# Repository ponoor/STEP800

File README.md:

# STEP800
8-axis stepper motor driver for Open Sound Control

STEP800 is a 8-axis stepper motor driver designed for art or design projects. STEP800 combines the following elements into one single board:

- [Arduino Zero](https://www.arduino.cc/en/Guide/ArduinoZero)
- Ethernet shield
- 8 stepper motor drivers
- Sensor inputs for homing

The current firmware is focused on working with [Open Sound Control](http://opensoundcontrol.org/) (OSC) via Ethernet, which is a common protocol for creative coding environments, like openFrameworks, Processing, Max, Unity, or Touch Designer.

Stepper driver chips are STMicroelectronics's [L6470](https://www.st.com/en/motor-drivers/l6470.html) which provide most of functionalities as a stepper driver.

Friend of STEP800 : [STEP400](https://github.com/ponoor/STEP400)

## Store
https://ponoor.com/en/shop/

## Documentation
https://ponoor.com/en/docs/step-series/

Forum: https://github.com/ponoor/step-series-support/discussions

## Repository Contents
### Firmware

**Important Note:**
The latest firmware is available at [STEP-series Universal Firmware](https://github.com/ponoor/step-series-universal-firmware) repository. Following directories and Releases are not maintained anymore. 

These 2 folders contain same codes.
- [/STEP800_firmware](https://github.com/ponoor/STEP800/tree/main/STEP800_firmware) : Arduino Sketch folder
- [/firmware-platformIO/STEP800_firmware](https://github.com/ponoor/STEP800/tree/main/firmware-platformIO/STEP800_firmware) : PlatformIO folder

### Hardware
[/hardware](https://github.com/ponoor/STEP800/tree/main/hardware) : Eagle design files, BOM lists, and a schematics PDF

### Others
[/configTool](https://github.com/ponoor/STEP800/tree/main/configTool) : The configuration tool consists of a html and JavaScritpts.

## Firmware dependency
- **[OSC Library](https://github.com/CNMAT/OSC)** from CNMAT
- **[Ponoor L6470 Library](https://github.com/ponoor/Ponoor_L6470_Library)**
- **[ArduinoJSON Library](https://arduinojson.org/)**
- **[Adafruit SleepyDog Arduino Library](https://github.com/adafruit/Adafruit_SleepyDog)**

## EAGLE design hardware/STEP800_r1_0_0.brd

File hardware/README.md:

# Diagram
```mermaid
flowchart LR
	MCU ---|SPI/SERCOM4| W5500 --- Ethernet
	MCU --- |SPI/SERCOM3|L6470 --> Motor
  MCU --> |SPI/SERCOM2|74HC165 --> 74HC595 --> MCU
	HomeSw -->|SW| L6470
	DIPSW --> 74HC165
	74HC595 --> Brake
  ```
  
  Check the [document](https://ponoor.com/en/docs/step-series/technical-information/hardware-step800/) for details.

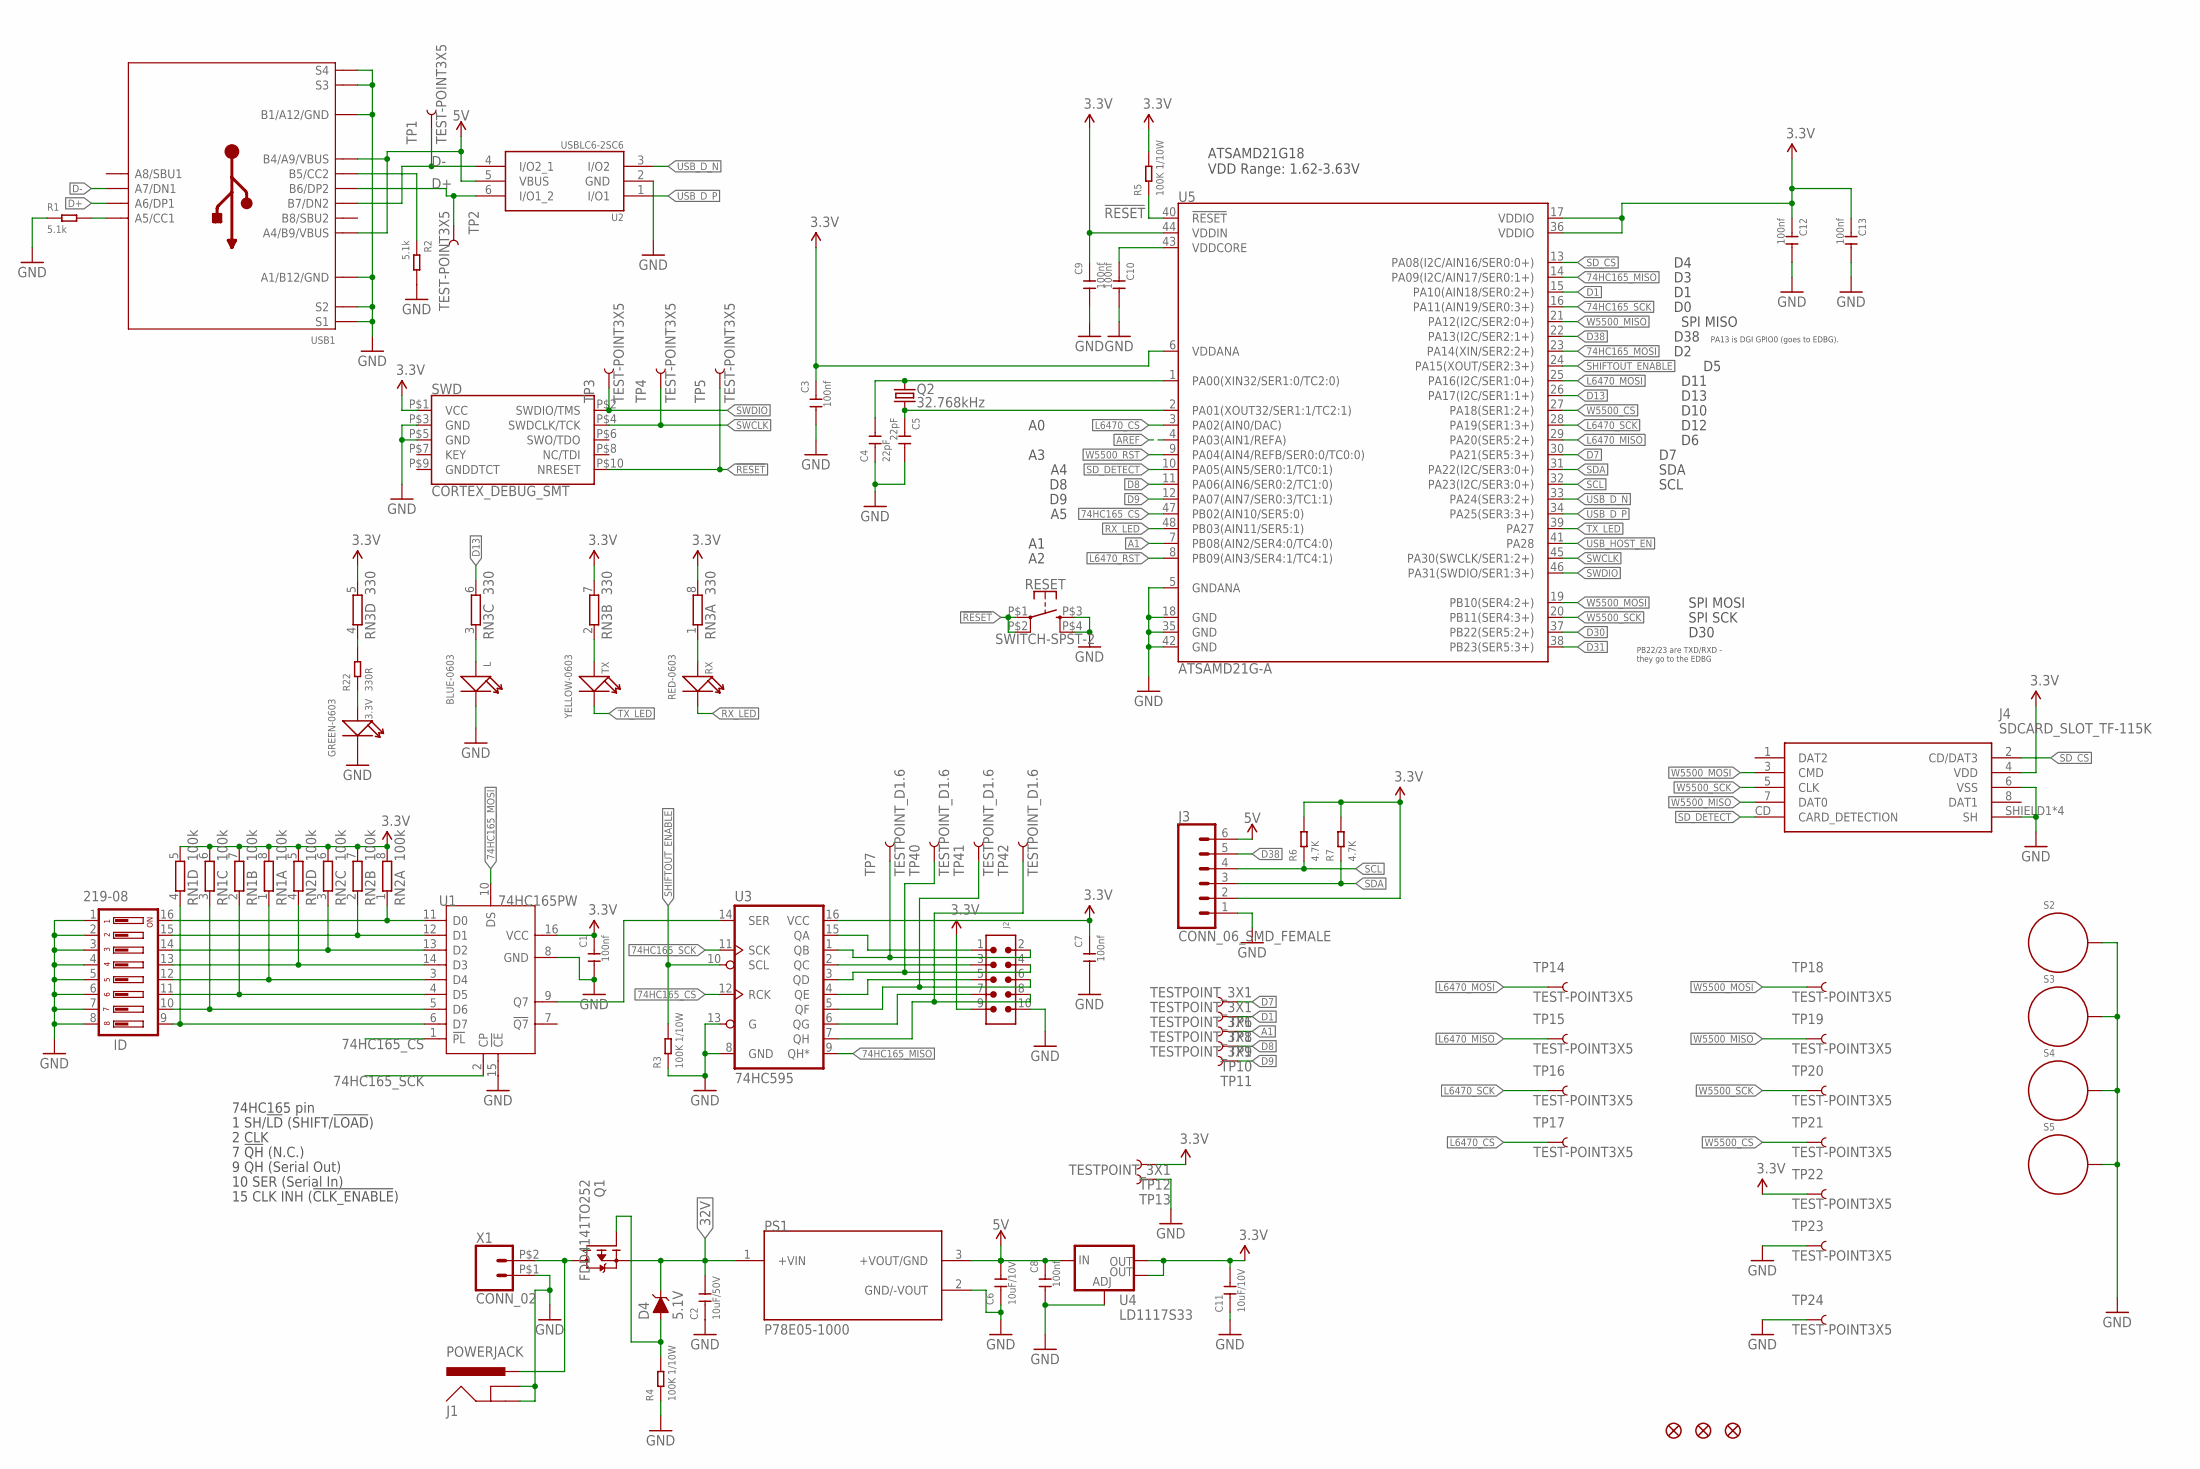
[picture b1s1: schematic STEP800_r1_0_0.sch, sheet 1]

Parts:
3.3V: GREEN-0603; LED-0603
C1, C3, C7, C8, C9, C10, C12, C13: 100nf; C0402
C2: 10uF/50V; C1206
C4, C5: 22pF; C0402
C6: 10uF/10V; C1206
C11: 10uF/10V; C0805
D4: 5.1V; SOD-323
FD1, FD2, FD3: FIDUCIAL1X2; FIDUCIAL-1X2
ID: 219-08; CTS-219-08
J1: POWERJACK; POWERJACK_SLOT
J2: 6120XX21621_61201021621; 61201021621
J3: CONN_06_SMD_FEMALE; 1X06-SMD-FEMALE
J4: SDCARD_SLOT_TF-115K; TF-115K
L: BLUE-0603; LED-0603
PS1: P78E05-1000; CONV_P78E05-1000
Q1: FDD4141TO252; TO252
Q2: 32.768kHz; FC-135
R1, R2: 5.1k; R0603
R3, R4, R5: 100K 1/10W; R0603
R6, R7: 4.7K; R0603
R22: 330R; R0603
RESET: SWITCH-SPST-2; SKRP
RN1, RN2: 100k; CAY16_LONG_W
RN3: 330; CAY16_LONG_W
RX: RED-0603; LED-0603
S2, S3, S4, S5: STANDOFF_ELECTRICAL; STANDOFF-ELECTRICAL
SWD: CORTEX_DEBUG_SMT; 20021121-00010C4LF
TP1, TP2, TP3, TP4, TP5, TP14, TP15, TP16, TP17, TP18, TP19, TP20, TP21, TP22, TP23, TP24: TEST-POINT3X5; PAD.03X.05
TP6, TP8, TP9, TP10, TP11, TP12, TP13: TESTPOINT_3X1
TP7, TP40, TP41, TP42: TESTPOINT_D1.6
TX: YELLOW-0603; LED-0603
U1: 74HC165PW; TSSOP16
U2: USBLC6-2SC6; SOT23-6L
U3: 74HC595; TSSOP16
U4: LD1117S33; SOT223
U5: ATSAMD21G-A; TQFP-48
USB1: USB-C_USB2.0-TYPE-C
X1: CONN_02; WJ25C-B-7.62-2P

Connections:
3.3V: C1.1, C3.1, C7.1, C9.1, C11.2, C12.1, C13.1, J2.9, J3.2, J4.4 (VDD), R5.2, R6.2, R7.2, RN1.5 (2), RN1.6 (2), RN1.7 (2), RN1.8 (2), RN2.5 (2), RN2.6 (2), RN2.7 (2), RN2.8 (2), RN3.5 (2), RN3.7 (2), RN3.8 (2), SWD.P$1 (VCC), TP12.P$1, TP22.P$1, U1.16 (VCC), U3.16 (VCC), U4.2 (OUT), U4.4 (OUT), U5.6 (VDDANA), U5.17 (VDDIO), U5.36 (VDDIO), U5.44 (VDDIN); also elsewhere on the board
5V: C6.2, C8.1, J3.6, PS1.3 (+VOUT/GND), U2.5 (VBUS), U4.3 (IN), USB1.A4_B9 (A4/B9/VBUS), USB1.B4_A9 (B4/A9/VBUS); also elsewhere on the board
32V: C2.2, D4.C, PS1.1 (+VIN), Q1.2 (S); also elsewhere on the board
74HC165_CS: U1.1 (!PL), U3.12 (RCK), U5.47 (PB02(AIN10/SER5:0))
74HC165_MISO: U3.9 (QH*), U5.14 (PA09(I2C/AIN17/SER0:1+))
74HC165_MOSI: U1.10 (DS), U5.23 (PA14(XIN/SER2:2+))
74HC165_SCK: U1.2 (CP), U3.11 (SCK), U5.16 (PA11(AIN19/SER0:3+))
!RESET: R5.1, RESET.P$1 (1), RESET.P$2 (2), SWD.P$10 (NRESET), TP5.P$1, U5.40 (!RESET!)
A1: TP9.P$1, U5.7 (PB08(AIN2/SER4:0/TC4:0))
AREF: U5.4 (PA03(AIN1/REFA))
D1: TP8.P$1, U5.15 (PA10(AIN18/SER0:2+))
D7: TP6.P$1, U5.30 (PA21(SER5:3+))
D8: TP10.P$1, U5.11 (PA06(AIN6/SER0:2/TC1:0))
D9: TP11.P$1, U5.12 (PA07(AIN7/SER0:3/TC1:1))
D13: RN3.6 (2), U5.26 (PA17(I2C/SER1:1+))
D30: U5.37 (PB22(SER5:2+))
D31: U5.38 (PB23(SER5:3+))
D38: J3.5, U5.22 (PA13(I2C/SER2:1+))
D+: TP2.P$1, U2.6 (I/O1_2), USB1.A6 (A6/DP1), USB1.B6 (B6/DP2)
D-: TP1.P$1, U2.4 (I/O2_1), USB1.A7 (A7/DN1), USB1.B7 (B7/DN2)
GND: 3.3V.-, C1.2, C2.1, C3.2, C4.1, C5.2, C6.1, C7.2, C8.2, C9.2, C10.2, C11.1, C12.2, C13.2, ID.1, ID.2, ID.3, ID.4, ID.5, ID.6, ID.7, ID.8, J1.P$33 (GNDBREAK), J1.P$34 (GNDBREAK), J1.P$35 (GNDBREAK), J1.P$36 (GNDBREAK), J1.P$37 (GNDBREAK), J1.P$38 (GNDBREAK), J1.P$39 (GNDBREAK), J1.P$40 (GNDBREAK), J1.P$41 (GNDBREAK), J1.P$42 (GNDBREAK), J1.P$43 (GNDBREAK), J1.P$44 (GNDBREAK), J1.P$45 (GNDBREAK), J1.P$46 (GNDBREAK), J1.P$47 (GNDBREAK), J1.P$48 (GNDBREAK), J1.P$49 (GNDBREAK), J1.P$50 (GNDBREAK), J1.P$51 (GNDBREAK), J1.P$52 (GNDBREAK), J1.P$53 (GNDBREAK), J1.P$54 (GNDBREAK), J1.P$55 (GNDBREAK), J1.P$56 (GNDBREAK), J1.P$63 (GND), J1.P$64 (GND), J1.P$65 (GND), J1.P$66 (GND), J1.P$67 (GND), J1.P$68 (GND), J1.P$69 (GND), J1.P$70 (GND), J1.P$71 (GND), J1.P$72 (GND), J1.P$73 (GND), J1.P$74 (GND), J1.P$75 (GND), J1.P$76 (GND), J1.P$77 (GND), J1.P$78 (GND), J1.P$79 (GND), J1.P$80 (GND), J1.P$81 (GND), J1.P$82 (GND), J1.P$83 (GND), J1.P$84 (GND), J1.P$85 (GND), J2.10, J3.1, J4.6 (VSS), J4.SHIELD1 (SH), J4.SHIELD2 (SH), J4.SHIELD3 (SH), J4.SHIELD4 (SH), L.-, PS1.2 (GND/-VOUT), R1.1, R2.2, R3.1, R4.1, RESET.P$3 (3), RESET.P$4 (4), S2.P1, S3.P1, S4.P1, S5.P1, SWD.P$3 (GND), SWD.P$5 (GND), TP13.P$1, TP23.P$1, TP24.P$1, U1.8 (GND), U1.15 (!CE), U2.2 (GND), U3.8 (GND), U3.13 (G), U4.1 (ADJ), U5.5 (GNDANA), U5.18 (GND), U5.35 (GND), U5.42 (GND), USB1.A1_B12 (A1/B12/GND), USB1.B1_A12 (B1/A12/GND), USB1.S7 (S1), USB1.S8 (S1), USB1.S9 (S1), USB1.S10 (S1), USB1.S11 (S1), USB1.S12 (S1), USB1.S13 (S1), USB1.S14 (S1), USB1.S15 (S1), USB1.S16 (S3), USB1.S17 (S3), USB1.S18 (S3), USB1.S19 (S3), USB1.S20 (S3), USB1.S21 (S3), USB1.S22 (S3), USB1.S23 (S3), USB1.S24 (S3), USB1.S25 (S3), USB1.S26 (S3), USB1.S27 (S3), USB1.S29 (S2), USB1.S30 (S2), USB1.S31 (S2), USB1.S32 (S2), USB1.S33 (S2), USB1.S34 (S2), USB1.S35 (S2), USB1.S36 (S2), USB1.S37 (S4), USB1.S38 (S4), USB1.S39 (S4), USB1.S40 (S4), USB1.S41 (S4), USB1.S42 (S4), USB1.S43 (S4), USB1.S44 (S4), USB1.S45 (S4), USB1.S46 (S4), USB1.S47 (S4), USB1.S48 (S4), X1.P$1 (1); also elsewhere on the board
L6470_CS: TP17.P$1, U5.3 (PA02(AIN0/DAC)); also elsewhere on the board
L6470_MISO: TP15.P$1, U5.29 (PA20(SER5:2+)); also elsewhere on the board
L6470_MOSI: TP14.P$1, U5.25 (PA16(I2C/SER1:0+)); also elsewhere on the board
L6470_RST: U5.8 (PB09(AIN3/SER4:1/TC4:1)); also elsewhere on the board
L6470_SCK: TP16.P$1, U5.28 (PA19(SER1:3+)); also elsewhere on the board
unnamed: C4.2, Q2.P$2 (2), U5.1 (PA00(XIN32/SER1:0/TC2:0))
unnamed: ID.16, RN2.1, U1.11 (D0)
unnamed: D4.A, Q1.1 (G), R4.2
unnamed: ID.15, RN2.2 (1), U1.12 (D1)
unnamed: ID.14, RN2.3 (1), U1.13 (D2)
unnamed: C5.1, Q2.P$1 (1), U5.2 (PA01(XOUT32/SER1:1/TC2:1))
unnamed: U1.9 (Q7), U3.14 (SER)
unnamed: RN3.1, RX.+
unnamed: ID.13, RN2.4 (1), U1.14 (D3)
unnamed: ID.12, RN1.1, U1.3 (D4)
unnamed: ID.11, RN1.2 (1), U1.4 (D5)
unnamed: RN3.2 (1), TX.+
unnamed: L.+, RN3.3 (1)
unnamed: R22.2, RN3.4 (1)
unnamed: J2.3, U3.2 (QC)
unnamed: ID.10, RN1.3 (1), U1.5 (D6)
unnamed: J2.2, TP7.1, U3.1 (QB)
unnamed: J2.1, U3.15 (QA)
unnamed: ID.9, RN1.4 (1), U1.6 (D7)
unnamed: J2.4, TP40.1, U3.3 (QD)
unnamed: J2.5, U3.4 (QE)
unnamed: J2.6, TP41.1, U3.5 (QF)
unnamed: J2.7, U3.6 (QG)
unnamed: J2.8, TP42.1, U3.7 (QH)
unnamed: R2.1, USB1.B5 (B5/CC2)
unnamed: 3.3V.+, R22.1
unnamed: R1.2, USB1.A5 (A5/CC1)
RX_LED: RX.-, U5.48 (PB03(AIN11/SER5:1))
SCL: J3.4, R6.1, U5.32 (PA23(I2C/SER3:0+))
SDA: J3.3, R7.1, U5.31 (PA22(I2C/SER3:0+))
SD_CS: J4.2 (CD/DAT3), U5.13 (PA08(I2C/AIN16/SER0:0+))
SD_DETECT: J4.CD (CARD_DETECTION), U5.10 (PA05(AIN5/SER0:1/TC0:1))
SHIFTOUT_ENABLE: R3.2, U3.10 (SCL), U5.24 (PA15(XOUT/SER2:3+))
SWCLK: SWD.P$4 (SWDCLK/TCK), TP4.P$1, U5.45 (PA30(SWCLK/SER1:2+))
SWDIO: SWD.P$2 (SWDIO/TMS), TP3.P$1, U5.46 (PA31(SWDIO/SER1:3+))
TX_LED: TX.-, U5.39 (PA27)
USB_D_N: U2.3 (I/O2), U5.33 (PA24(SER3:2+))
USB_D_P: U2.1 (I/O1), U5.34 (PA25(SER3:3+))
USB_HOST_EN: U5.41 (PA28)
VDDCORE1: C10.1, U5.43 (VDDCORE)
VRAW: J1.P$2 (PWR), J1.P$3 (PWR), J1.P$4 (PWR), J1.P$5 (PWR), J1.P$6 (PWR), J1.P$7 (PWR), J1.P$8 (PWR), J1.P$9 (PWR), J1.P$10 (PWR), J1.P$11 (PWR), J1.P$12 (PWR), J1.P$13 (PWR), J1.P$14 (PWR), J1.P$15 (PWR), J1.P$16 (PWR), J1.P$17 (PWR), J1.P$18 (PWR), J1.P$19 (PWR), J1.P$20 (PWR), J1.P$21 (PWR), J1.P$22 (PWR), J1.P$23 (PWR), J1.P$24 (PWR), J1.P$25 (PWR), J1.P$26 (PWR), J1.P$27 (PWR), J1.P$28 (PWR), Q1.3 (D), X1.P$2 (2)
W5500_CS: TP21.P$1, U5.27 (PA18(SER1:2+)); also elsewhere on the board
W5500_MISO: J4.7 (DAT0), TP19.P$1, U5.21 (PA12(I2C/SER2:0+)); also elsewhere on the board
W5500_MOSI: J4.3 (CMD), TP18.P$1, U5.19 (PB10(SER4:2+)); also elsewhere on the board
W5500_RST: U5.9 (PA04(AIN4/REFB/SER0:0/TC0:0)); also elsewhere on the board
W5500_SCK: J4.5 (CLK), TP20.P$1, U5.20 (PB11(SER4:3+)); also elsewhere on the board

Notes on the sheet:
PB22/23 are TXD/RXD - they go to the EDBG
PA13 is DGI GPIO0 (goes to EDBG).
ATSAMD21G18 VDD Range: 1.62-3.63V
D30
D12
D10
D11
D13
D38
SPI MISO
SPI MOSI
SPI SCK
SDA
SCL
1 SH/!LD! (SHIFT/!LOAD!)
2 CLK
7 !QH! (N.C.)
9 QH (Serial Out)
10 SER (Serial In)
15 CLK INH (!CLK_ENABLE!)
74HC165 pin

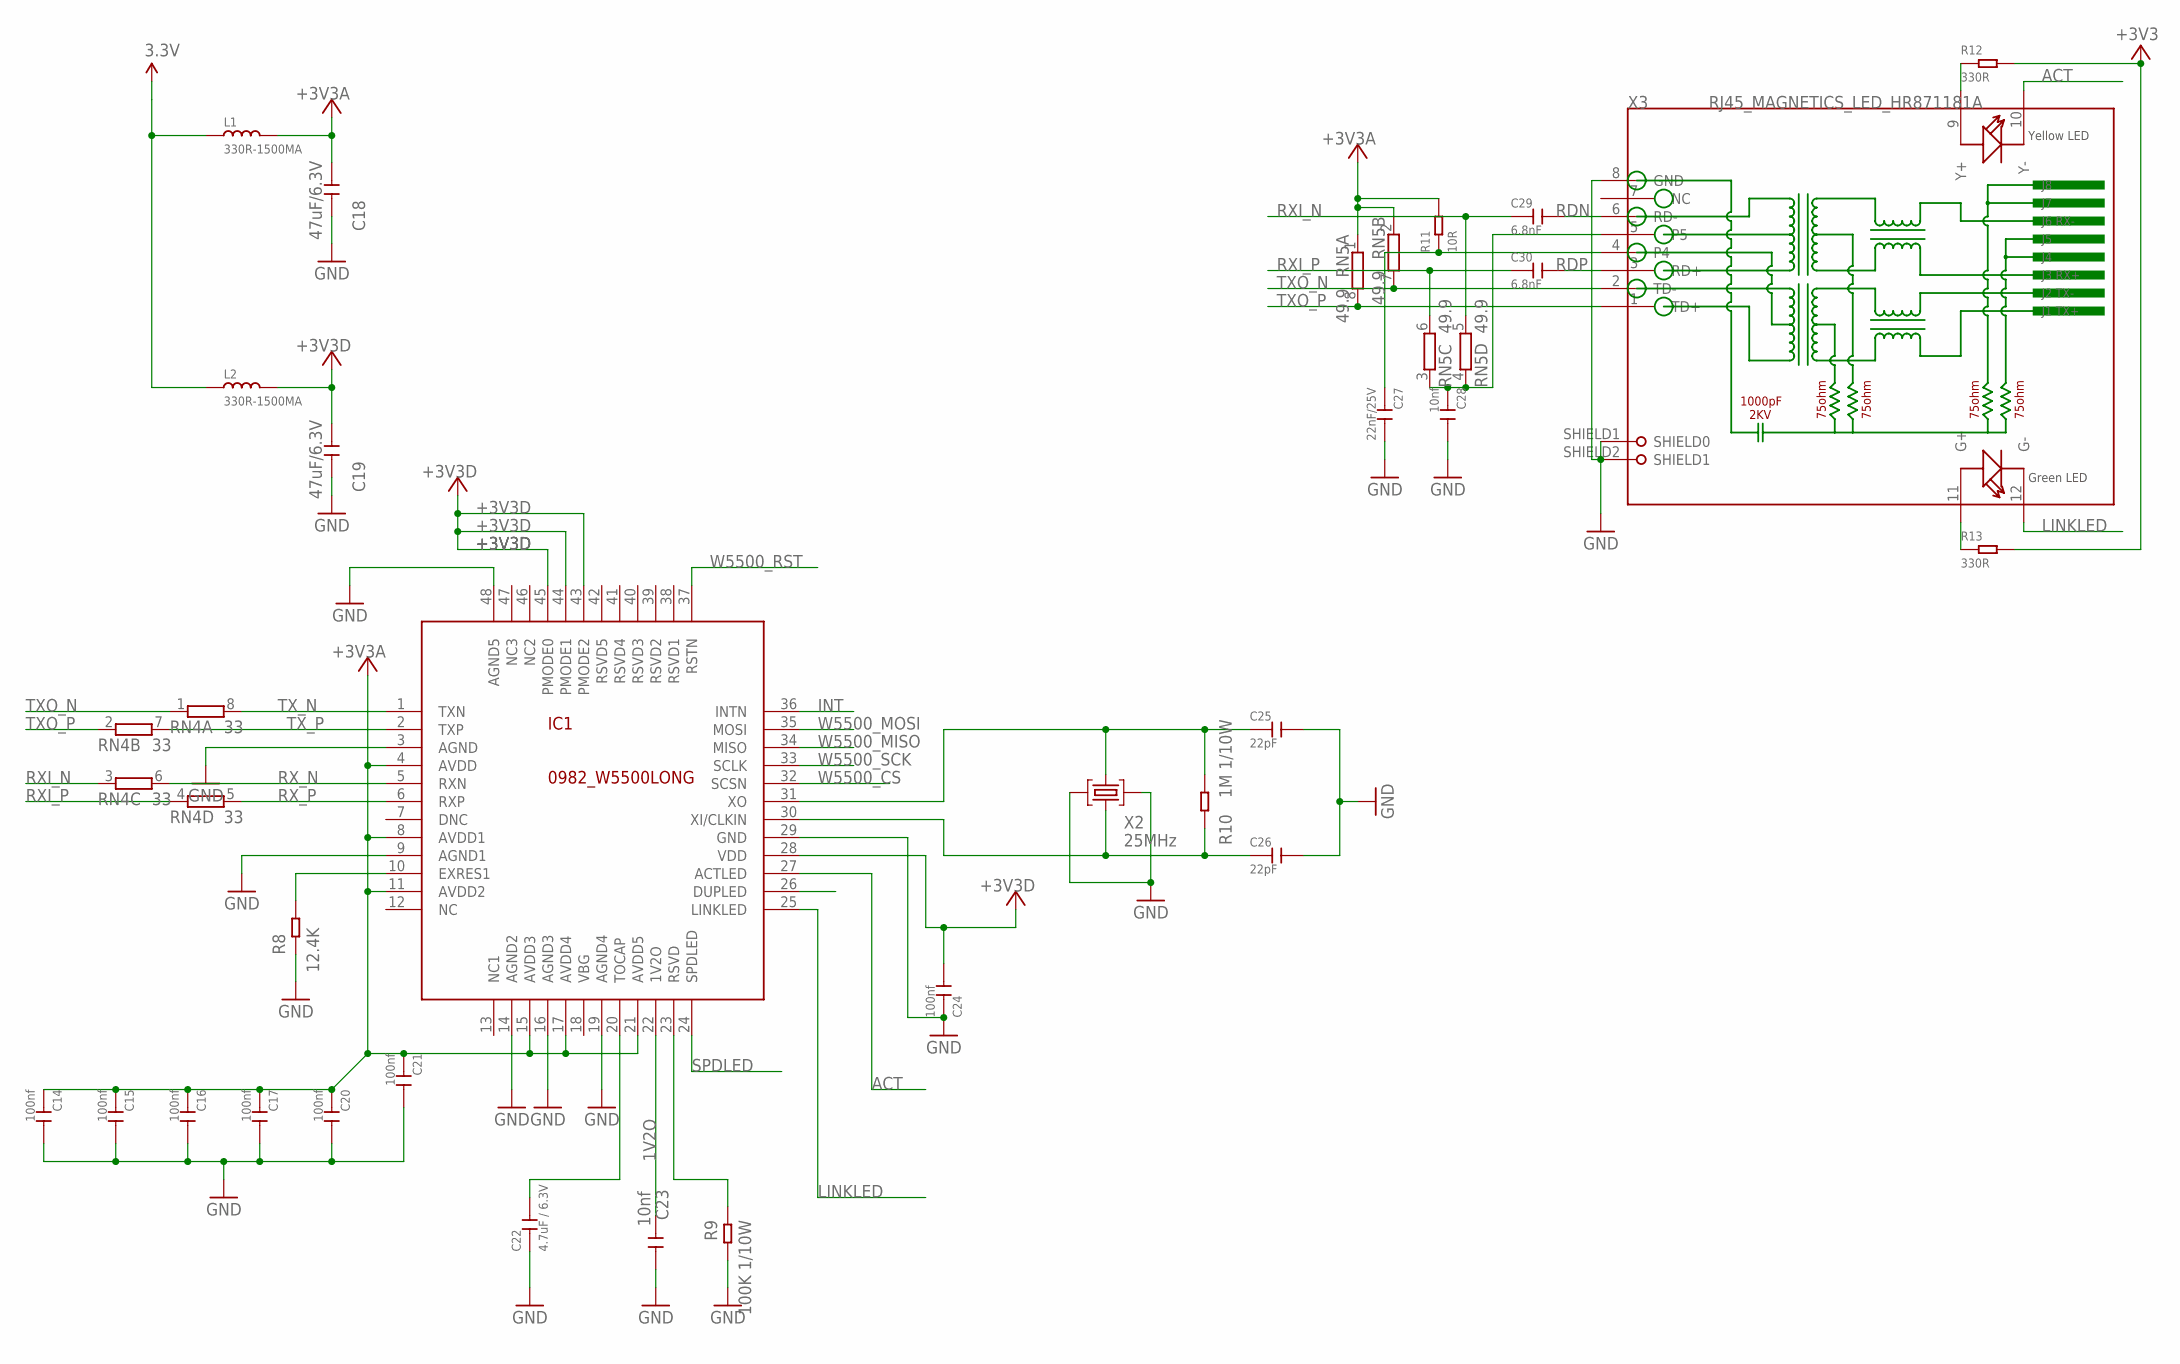
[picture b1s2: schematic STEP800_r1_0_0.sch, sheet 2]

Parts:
C14, C15, C16, C17, C20, C21, C24: 100nf; C0402
C18, C19: 47uF/6.3V; C1206
C22: 4.7uF / 6.3V; C0603
C23, C28: 10nf; C0603
C25, C26: 22pF; C0402
C27: 22nF/25V; C0402
C29, C30: 6.8nF; C0402
IC1: 0982_W5500LONG; TQFP48-LONG
L1, L2: 330R-1500MA; L0805
R8: 12.4K; R0603
R9: 100K 1/10W; R0603
R10: 1M 1/10W; R0603
R11: 10R; R0603
R12, R13: 330R; R0603
RN4: 33; CAY16_LONG_W
RN5: 49.9; CAY16_LONG_W
X2: 25MHz; CRYSTAL-3.2-2.5
X3: RJ45_MAGNETICS_LED_HR871181A; HR871181A

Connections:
1V2O: C23.2, IC1.22 (1V2O)
3.3V: L1.1, L2.1, R12.2, R13.2; also elsewhere on the board
+3V3A: C14.1, C15.1, C16.1, C17.1, C18.1, C20.1, C21.1, IC1.4 (AVDD), IC1.8 (AVDD1), IC1.11 (AVDD2), IC1.15 (AVDD3), IC1.17 (AVDD4), IC1.21 (AVDD5), L1.2, R11.2, RN5.1, RN5.2 (1)
+3V3D: C19.1, C24.2, IC1.28 (VDD), IC1.43 (PMODE2), IC1.44 (PMODE1), IC1.45 (PMODE0), L2.2
ACT: IC1.27 (ACTLED), X3.10 (Y-)
FDXLED1: IC1.26 (DUPLED)
GND: C14.2, C15.2, C16.2, C17.2, C18.2, C19.2, C20.2, C21.2, C22.1, C23.1, C24.1, C25.2, C26.2, C27.2, C28.2, IC1.3 (AGND), IC1.9 (AGND1), IC1.14 (AGND2), IC1.16 (AGND3), IC1.19 (AGND4), IC1.29 (GND), IC1.48 (AGND5), R8.1, R9.1, X2.2 (GND), X2.4 (GND), X3.8 (GND), X3.SHIELD1 (SHIELD0), X3.SHIELD2 (SHIELD1); also elsewhere on the board
INT: IC1.36 (INTN)
LINKLED: IC1.25 (LINKLED), X3.12 (G-)
unnamed: C25.1, IC1.31 (XO), R10.1, X2.3 (C2)
unnamed: IC1.23 (RSVD), R9.2
unnamed: IC1.10 (EXRES1), R8.2
unnamed: C22.2, IC1.20 (TOCAP)
unnamed: C27.1, R11.1, X3.4
unnamed: C28.1, RN5.3 (1), RN5.4 (1), X3.5
unnamed: R12.1, X3.9 (Y+)
unnamed: R13.1, X3.11 (G+)
NC: IC1.12 (NC)
OSC2E1: C26.1, IC1.30 (XI/CLKIN), R10.2, X2.1 (C1)
RDN: C29.2, X3.6 (RD-)
RDP: C30.2, X3.3 (RD+)
RSVD1: IC1.38 (RSVD1)
RSVD2: IC1.39 (RSVD2)
RSVD3: IC1.40 (RSVD3)
RXI_N: C29.1, RN4.3 (1), RN5.5 (2)
RXI_P: C30.1, RN4.4 (1), RN5.6 (2)
RX_N: IC1.5 (RXN), RN4.6 (2)
RX_P: IC1.6 (RXP), RN4.5 (2)
SPDLED: IC1.24 (SPDLED)
TXO_N: RN4.1, RN5.7 (2), X3.2 (TD-)
TXO_P: RN4.2 (1), RN5.8 (2), X3.1 (TD+)
TX_N: IC1.1 (TXN), RN4.8 (2)
TX_P: IC1.2 (TXP), RN4.7 (2)
W5500_CS: IC1.32 (SCSN); also elsewhere on the board
W5500_MISO: IC1.34 (MISO); also elsewhere on the board
W5500_MOSI: IC1.35 (MOSI); also elsewhere on the board
W5500_RST: IC1.37 (RSTN); also elsewhere on the board
W5500_SCK: IC1.33 (SCLK); also elsewhere on the board

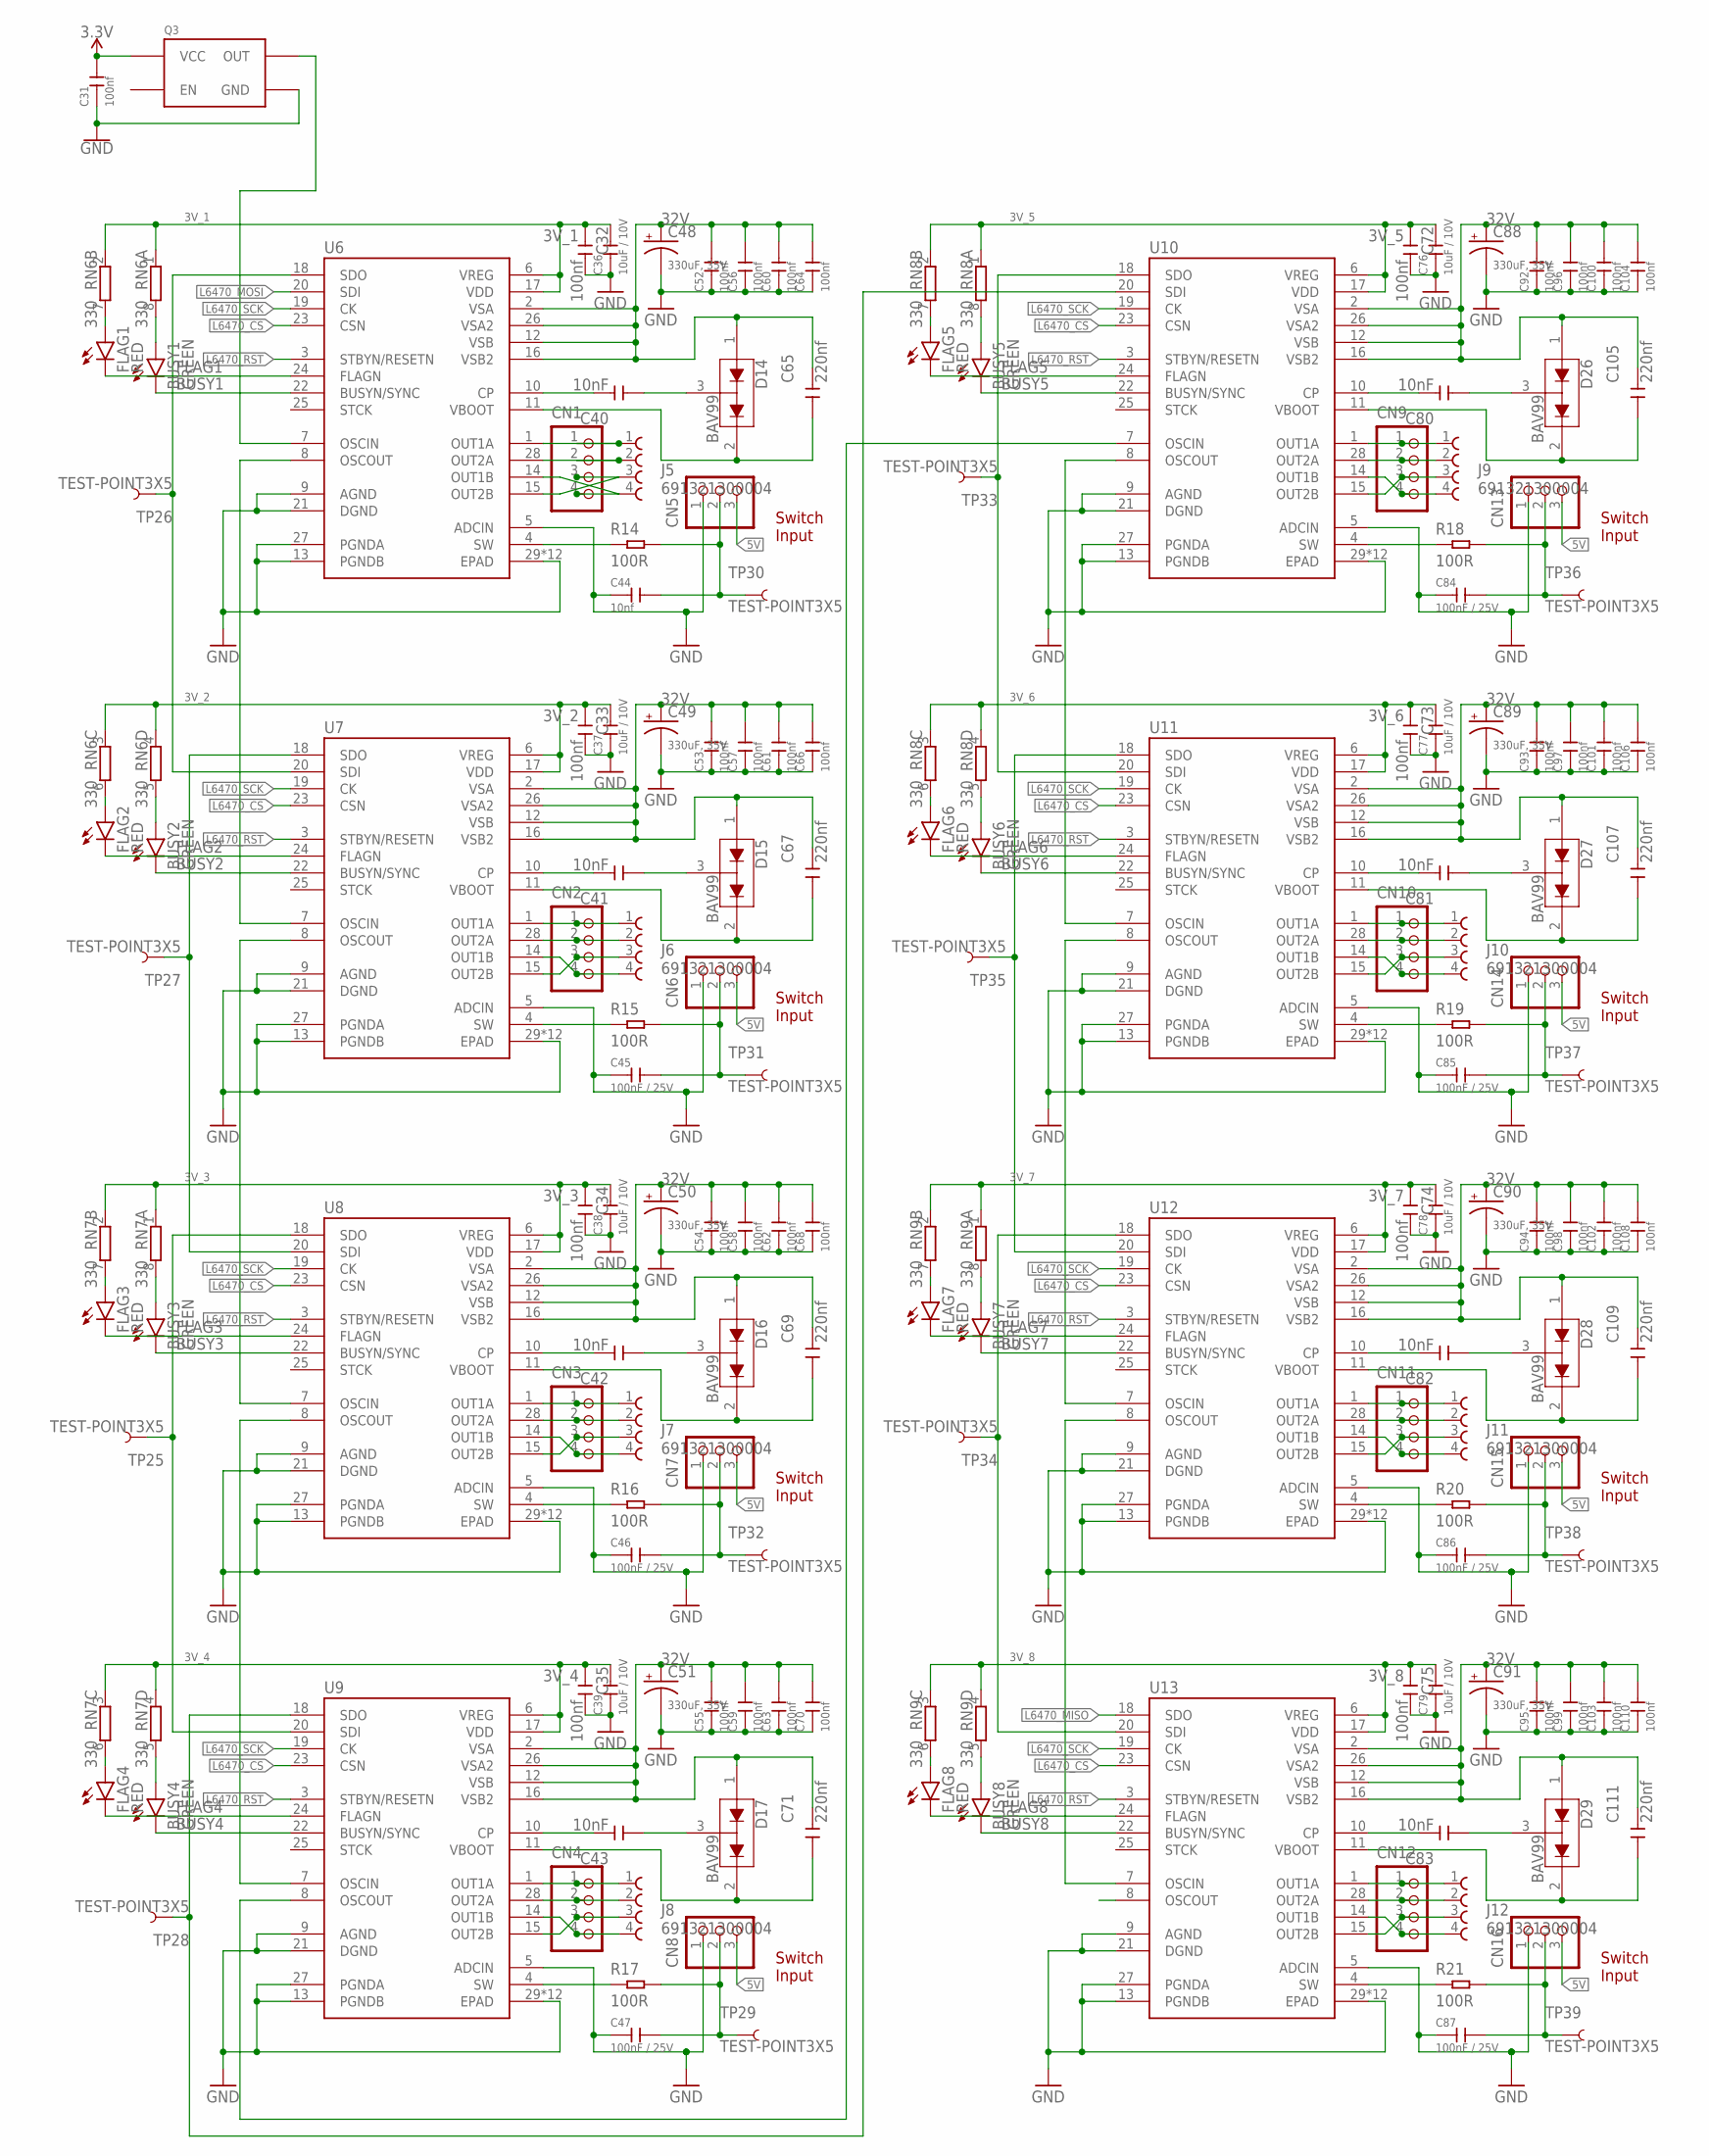
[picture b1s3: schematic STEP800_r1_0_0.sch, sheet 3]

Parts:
BUSY1, BUSY2, BUSY3, BUSY4, BUSY5, BUSY6, BUSY7, BUSY8: GREEN; LED-0603
C31, C32, C33, C34, C35, C72, C73, C74, C75: 100nf; C0402
C36, C37, C38, C39, C76, C77, C78, C79: 10uF / 10V; C0805
C40, C41, C42, C43, C80, C81, C82, C83: 10nF; C0603
C44: 10nf; C0402
C45, C46, C47, C84, C85, C86, C87: 100nF / 25V; C0402
C48, C49, C50, C51, C88, C89, C90, C91: 330uF, 35V; NICHICON_D10
C52, C53, C54, C55, C56, C57, C58, C59, C60, C61, C62, C63, C64, C66, C68, C70, C92, C93, C94, C95, C96, C97, C98, C99, C100, C101, C102, C103, C104, C106, C108, C110: 100nf; C0603
C65, C67, C69, C71, C105, C107, C109, C111: 220nf; C0603
CN1, CN2, CN3, CN4, CN9, CN10, CN11, CN12: B4B-XASK-1
CN5, CN6, CN7, CN8, CN13, CN14, CN15, CN16: B3B-XASK-1
D14, D15, D16, D17, D26, D27, D28, D29: BAV99; SOT23-3
FLAG1, FLAG2, FLAG3, FLAG4, FLAG5, FLAG6, FLAG7, FLAG8: RED; LED-0603
J5, J6, J7, J8, J9, J10, J11, J12: 691321300004
Q3: CRYSTAL_OSC_SG5032; SG5032
R14, R15, R16, R17, R18, R19, R20, R21: 100R; R0603
RN6, RN7, RN8, RN9: 330; CAY16_LONG_W
TP25, TP26, TP27, TP28, TP29, TP30, TP31, TP32, TP33, TP34, TP35, TP36, TP37, TP38, TP39: TEST-POINT3X5; PAD.03X.05
U6, U7, U8, U9, U10, U11, U12, U13: L6470_THERMALVIA; HTSSOP28_VIA

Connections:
3.3V: C31.2, Q3.4 (VCC); also elsewhere on the board
3V_1: C32.1, C36.2, RN6.1, RN6.2 (1), U6.6 (VREG), U6.17 (VDD)
3V_2: C33.1, C37.2, RN6.3 (1), RN6.4 (1), U7.6 (VREG), U7.17 (VDD)
3V_3: C34.1, C38.2, RN7.1, RN7.2 (1), U8.6 (VREG), U8.17 (VDD)
3V_4: C35.1, C39.2, RN7.3 (1), RN7.4 (1), U9.6 (VREG), U9.17 (VDD)
3V_5: C72.1, C76.2, RN8.1, RN8.2 (1), U10.6 (VREG), U10.17 (VDD)
3V_6: C73.1, C77.2, RN8.3 (1), RN8.4 (1), U11.6 (VREG), U11.17 (VDD)
3V_7: C74.1, C78.2, RN9.1, RN9.2 (1), U12.6 (VREG), U12.17 (VDD)
3V_8: C75.1, C79.2, RN9.3 (1), RN9.4 (1), U13.6 (VREG), U13.17 (VDD)
5V: CN5.3, CN6.3, CN7.3, CN8.3, CN13.3, CN14.3, CN15.3, CN16.3; also elsewhere on the board
32V: C48.+, C49.+, C50.+, C51.+, C52.2, C53.2, C54.2, C55.2, C56.2, C57.2, C58.2, C59.2, C60.2, C61.2, C62.2, C63.2, C64.2, C65.2, C66.2, C67.2, C68.2, C69.2, C70.2, C71.2, C88.+, C89.+, C90.+, C91.+, C92.2, C93.2, C94.2, C95.2, C96.2, C97.2, C98.2, C99.2, C100.2, C101.2, C102.2, C103.2, C104.2, C105.2, C106.2, C107.2, C108.2, C109.2, C110.2, C111.2, D14.1 (A1), D15.1 (A1), D16.1 (A1), D17.1 (A1), D26.1 (A1), D27.1 (A1), D28.1 (A1), D29.1 (A1), U6.2 (VSA), U6.12 (VSB), U6.16 (VSB2), U6.26 (VSA2), U7.2 (VSA), U7.12 (VSB), U7.16 (VSB2), U7.26 (VSA2), U8.2 (VSA), U8.12 (VSB), U8.16 (VSB2), U8.26 (VSA2), U9.2 (VSA), U9.12 (VSB), U9.16 (VSB2), U9.26 (VSA2), U10.2 (VSA), U10.12 (VSB), U10.16 (VSB2), U10.26 (VSA2), U11.2 (VSA), U11.12 (VSB), U11.16 (VSB2), U11.26 (VSA2), U12.2 (VSA), U12.12 (VSB), U12.16 (VSB2), U12.26 (VSA2), U13.2 (VSA), U13.12 (VSB), U13.16 (VSB2), U13.26 (VSA2); also elsewhere on the board
BUSY1: BUSY1.C, U6.22 (BUSYN/SYNC)
BUSY2: BUSY2.C, U7.22 (BUSYN/SYNC)
BUSY3: BUSY3.C, U8.22 (BUSYN/SYNC)
BUSY4: BUSY4.C, U9.22 (BUSYN/SYNC)
BUSY5: BUSY5.C, U10.22 (BUSYN/SYNC)
BUSY6: BUSY6.C, U11.22 (BUSYN/SYNC)
BUSY7: BUSY7.C, U12.22 (BUSYN/SYNC)
BUSY8: BUSY8.C, U13.22 (BUSYN/SYNC)
FLAG1: FLAG1.C, U6.24 (FLAGN)
FLAG2: FLAG2.C, U7.24 (FLAGN)
FLAG3: FLAG3.C, U8.24 (FLAGN)
FLAG4: FLAG4.C, U9.24 (FLAGN)
FLAG5: FLAG5.C, U10.24 (FLAGN)
FLAG6: FLAG6.C, U11.24 (FLAGN)
FLAG7: FLAG7.C, U12.24 (FLAGN)
FLAG8: FLAG8.C, U13.24 (FLAGN)
GND: C31.1, C32.2, C33.2, C34.2, C35.2, C36.1, C37.1, C38.1, C39.1, C44.1, C45.1, C46.1, C47.1, C48.-, C49.-, C50.-, C51.-, C52.1, C53.1, C54.1, C55.1, C56.1, C57.1, C58.1, C59.1, C60.1, C61.1, C62.1, C63.1, C64.1, C66.1, C68.1, C70.1, C72.2, C73.2, C74.2, C75.2, C76.1, C77.1, C78.1, C79.1, C84.1, C85.1, C86.1, C87.1, C88.-, C89.-, C90.-, C91.-, C92.1, C93.1, C94.1, C95.1, C96.1, C97.1, C98.1, C99.1, C100.1, C101.1, C102.1, C103.1, C104.1, C106.1, C108.1, C110.1, CN5.1, CN6.1, CN7.1, CN8.1, CN13.1, CN14.1, CN15.1, CN16.1, Q3.2 (GND), U6.5 (ADCIN), U6.9 (AGND), U6.13 (PGNDB), U6.21 (DGND), U6.27 (PGNDA), U6.29 (EPAD), U6.VIA1 (EPAD), U6.VIA2 (EPAD), U6.VIA3 (EPAD), U6.VIA4 (EPAD), U6.VIA5 (EPAD), U6.VIA6 (EPAD), U6.VIA7 (EPAD), U6.VIA8 (EPAD), U6.VIA9 (EPAD), U6.VIA10 (EPAD), U6.VIA11 (EPAD), U7.5 (ADCIN), U7.9 (AGND), U7.13 (PGNDB), U7.21 (DGND), U7.27 (PGNDA), U7.29 (EPAD), U7.VIA1 (EPAD), U7.VIA2 (EPAD), U7.VIA3 (EPAD), U7.VIA4 (EPAD), U7.VIA5 (EPAD), U7.VIA6 (EPAD), U7.VIA7 (EPAD), U7.VIA8 (EPAD), U7.VIA9 (EPAD), U7.VIA10 (EPAD), U7.VIA11 (EPAD), U8.5 (ADCIN), U8.9 (AGND), U8.13 (PGNDB), U8.21 (DGND), U8.27 (PGNDA), U8.29 (EPAD), U8.VIA1 (EPAD), U8.VIA2 (EPAD), U8.VIA3 (EPAD), U8.VIA4 (EPAD), U8.VIA5 (EPAD), U8.VIA6 (EPAD), U8.VIA7 (EPAD), U8.VIA8 (EPAD), U8.VIA9 (EPAD), U8.VIA10 (EPAD), U8.VIA11 (EPAD), U9.5 (ADCIN), U9.9 (AGND), U9.13 (PGNDB), U9.21 (DGND), U9.27 (PGNDA), U9.29 (EPAD), U9.VIA1 (EPAD), U9.VIA2 (EPAD), U9.VIA3 (EPAD), U9.VIA4 (EPAD), U9.VIA5 (EPAD), U9.VIA6 (EPAD), U9.VIA7 (EPAD), U9.VIA8 (EPAD), U9.VIA9 (EPAD), U9.VIA10 (EPAD), U9.VIA11 (EPAD), U10.5 (ADCIN), U10.9 (AGND), U10.13 (PGNDB), U10.21 (DGND), U10.27 (PGNDA), U10.29 (EPAD), U10.VIA1 (EPAD), U10.VIA2 (EPAD), U10.VIA3 (EPAD), U10.VIA4 (EPAD), U10.VIA5 (EPAD), U10.VIA6 (EPAD), U10.VIA7 (EPAD), U10.VIA8 (EPAD), U10.VIA9 (EPAD), U10.VIA10 (EPAD), U10.VIA11 (EPAD), U11.5 (ADCIN), U11.9 (AGND), U11.13 (PGNDB), U11.21 (DGND), U11.27 (PGNDA), U11.29 (EPAD), U11.VIA1 (EPAD), U11.VIA2 (EPAD), U11.VIA3 (EPAD), U11.VIA4 (EPAD), U11.VIA5 (EPAD), U11.VIA6 (EPAD), U11.VIA7 (EPAD), U11.VIA8 (EPAD), U11.VIA9 (EPAD), U11.VIA10 (EPAD), U11.VIA11 (EPAD), U12.5 (ADCIN), U12.9 (AGND), U12.13 (PGNDB), U12.21 (DGND), U12.27 (PGNDA), U12.29 (EPAD), U12.VIA1 (EPAD), U12.VIA2 (EPAD), U12.VIA3 (EPAD), U12.VIA4 (EPAD), U12.VIA5 (EPAD), U12.VIA6 (EPAD), U12.VIA7 (EPAD), U12.VIA8 (EPAD), U12.VIA9 (EPAD), U12.VIA10 (EPAD), U12.VIA11 (EPAD), U13.5 (ADCIN), U13.9 (AGND), U13.13 (PGNDB), U13.21 (DGND), U13.27 (PGNDA), U13.29 (EPAD), U13.VIA1 (EPAD), U13.VIA2 (EPAD), U13.VIA3 (EPAD), U13.VIA4 (EPAD), U13.VIA5 (EPAD), U13.VIA6 (EPAD), U13.VIA7 (EPAD), U13.VIA8 (EPAD), U13.VIA9 (EPAD), U13.VIA10 (EPAD), U13.VIA11 (EPAD); also elsewhere on the board
L6470_CS: U6.23 (CSN), U7.23 (CSN), U8.23 (CSN), U9.23 (CSN), U10.23 (CSN), U11.23 (CSN), U12.23 (CSN), U13.23 (CSN); also elsewhere on the board
L6470_MISO: U13.18 (SDO); also elsewhere on the board
L6470_MOSI: U6.20 (SDI); also elsewhere on the board
L6470_RST: U6.3 (STBYN/RESETN), U7.3 (STBYN/RESETN), U8.3 (STBYN/RESETN), U9.3 (STBYN/RESETN), U10.3 (STBYN/RESETN), U11.3 (STBYN/RESETN), U12.3 (STBYN/RESETN), U13.3 (STBYN/RESETN); also elsewhere on the board
L6470_SCK: U6.19 (CK), U7.19 (CK), U8.19 (CK), U9.19 (CK), U10.19 (CK), U11.19 (CK), U12.19 (CK), U13.19 (CK); also elsewhere on the board
unnamed: C40.2, U6.10 (CP)
unnamed: C40.1, D14.3 (COM)
unnamed: C65.1, D14.2 (C2), U6.11 (VBOOT)
unnamed: R14.1, U6.4 (SW)
unnamed: BUSY1.A, RN6.8 (2)
unnamed: FLAG1.A, RN6.7 (2)
unnamed: C44.2, CN5.2, R14.2, TP30.P$1
unnamed: CN1.1, J5.1, U6.1 (OUT1A)
unnamed: CN1.2, J5.2, U6.28 (OUT2A)
unnamed: CN1.4, J5.4, U6.14 (OUT1B)
unnamed: CN1.3, J5.3, U6.15 (OUT2B)
unnamed: TP26.P$1, U6.18 (SDO), U7.20 (SDI)
unnamed: C41.2, U7.10 (CP)
unnamed: C41.1, D15.3 (COM)
unnamed: C67.1, D15.2 (C2), U7.11 (VBOOT)
unnamed: R15.1, U7.4 (SW)
unnamed: BUSY2.A, RN6.5 (2)
unnamed: FLAG2.A, RN6.6 (2)
unnamed: C45.2, CN6.2, R15.2, TP31.P$1
unnamed: CN2.1, J6.1, U7.1 (OUT1A)
unnamed: CN2.2, J6.2, U7.28 (OUT2A)
unnamed: CN2.4, J6.4, U7.14 (OUT1B)
unnamed: CN2.3, J6.3, U7.15 (OUT2B)
unnamed: TP27.P$1, U7.18 (SDO), U8.20 (SDI)
unnamed: C42.2, U8.10 (CP)
unnamed: C42.1, D16.3 (COM)
unnamed: C69.1, D16.2 (C2), U8.11 (VBOOT)
unnamed: R16.1, U8.4 (SW)
unnamed: BUSY3.A, RN7.8 (2)
unnamed: FLAG3.A, RN7.7 (2)
unnamed: C46.2, CN7.2, R16.2, TP32.P$1
unnamed: CN3.1, J7.1, U8.1 (OUT1A)
unnamed: CN3.2, J7.2, U8.28 (OUT2A)
unnamed: CN3.4, J7.4, U8.14 (OUT1B)
unnamed: CN3.3, J7.3, U8.15 (OUT2B)
unnamed: TP25.P$1, U8.18 (SDO), U9.20 (SDI)
unnamed: C43.2, U9.10 (CP)
unnamed: C43.1, D17.3 (COM)
unnamed: C71.1, D17.2 (C2), U9.11 (VBOOT)
unnamed: R17.1, U9.4 (SW)
unnamed: BUSY4.A, RN7.5 (2)
unnamed: FLAG4.A, RN7.6 (2)
unnamed: C47.2, CN8.2, R17.2, TP29.P$1
unnamed: CN4.1, J8.1, U9.1 (OUT1A)
unnamed: CN4.2, J8.2, U9.28 (OUT2A)
unnamed: CN4.4, J8.4, U9.14 (OUT1B)
unnamed: CN4.3, J8.3, U9.15 (OUT2B)
unnamed: TP28.P$1, U9.18 (SDO), U10.20 (SDI)
unnamed: C80.2, U10.10 (CP)
unnamed: C80.1, D26.3 (COM)
unnamed: C105.1, D26.2 (C2), U10.11 (VBOOT)
unnamed: R18.1, U10.4 (SW)
unnamed: BUSY5.A, RN8.8 (2)
unnamed: FLAG5.A, RN8.7 (2)
unnamed: C84.2, CN13.2, R18.2, TP36.P$1
unnamed: CN9.1, J9.1, U10.1 (OUT1A)
unnamed: CN9.2, J9.2, U10.28 (OUT2A)
unnamed: CN9.4, J9.4, U10.14 (OUT1B)
unnamed: CN9.3, J9.3, U10.15 (OUT2B)
unnamed: TP33.P$1, U10.18 (SDO), U11.20 (SDI)
unnamed: C81.2, U11.10 (CP)
unnamed: C81.1, D27.3 (COM)
unnamed: C107.1, D27.2 (C2), U11.11 (VBOOT)
unnamed: R19.1, U11.4 (SW)
unnamed: BUSY6.A, RN8.5 (2)
unnamed: FLAG6.A, RN8.6 (2)
unnamed: C85.2, CN14.2, R19.2, TP37.P$1
unnamed: CN10.1, J10.1, U11.1 (OUT1A)
unnamed: CN10.2, J10.2, U11.28 (OUT2A)
unnamed: CN10.4, J10.4, U11.14 (OUT1B)
unnamed: CN10.3, J10.3, U11.15 (OUT2B)
unnamed: TP35.P$1, U11.18 (SDO), U12.20 (SDI)
unnamed: C82.2, U12.10 (CP)
unnamed: C82.1, D28.3 (COM)
unnamed: C109.1, D28.2 (C2), U12.11 (VBOOT)
unnamed: R20.1, U12.4 (SW)
unnamed: BUSY7.A, RN9.8 (2)
unnamed: FLAG7.A, RN9.7 (2)
unnamed: C86.2, CN15.2, R20.2, TP38.P$1
unnamed: CN11.1, J11.1, U12.1 (OUT1A)
unnamed: CN11.2, J11.2, U12.28 (OUT2A)
unnamed: CN11.4, J11.4, U12.14 (OUT1B)
unnamed: CN11.3, J11.3, U12.15 (OUT2B)
unnamed: TP34.P$1, U12.18 (SDO), U13.20 (SDI)
unnamed: C83.2, U13.10 (CP)
unnamed: C83.1, D29.3 (COM)
unnamed: C111.1, D29.2 (C2), U13.11 (VBOOT)
unnamed: R21.1, U13.4 (SW)
unnamed: BUSY8.A, RN9.5 (2)
unnamed: FLAG8.A, RN9.6 (2)
unnamed: C87.2, CN16.2, R21.2, TP39.P$1
unnamed: CN12.1, J12.1, U13.1 (OUT1A)
unnamed: CN12.2, J12.2, U13.28 (OUT2A)
unnamed: CN12.4, J12.4, U13.14 (OUT1B)
unnamed: CN12.3, J12.3, U13.15 (OUT2B)
OSCOUT2: U6.8 (OSCOUT), U7.7 (OSCIN)
OSCOUT4: U7.8 (OSCOUT), U8.7 (OSCIN)
OSCOUT6: U8.8 (OSCOUT), U9.7 (OSCIN)
OSCOUT8: U9.8 (OSCOUT), U10.7 (OSCIN)
OSCOUT10: U10.8 (OSCOUT), U11.7 (OSCIN)
OSCOUT12: U11.8 (OSCOUT), U12.7 (OSCIN)
OSCOUT14: U12.8 (OSCOUT), U13.7 (OSCIN)
OSCOUT16: U13.8 (OSCOUT)
QGOUT1: Q3.3 (OUT), U6.7 (OSCIN)

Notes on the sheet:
Switch Input

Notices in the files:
parts and their libraries:
SparkFun-Electromechanical: Licensing: Creative Commons ShareAlike 4.0 International - https://creativecommons.org/licenses/by-sa/4.0
Wurth_Connectors_WR-BHD: Copyright: Würth Elektronik
